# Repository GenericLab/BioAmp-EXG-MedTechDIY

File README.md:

Thanks a lot to the team at UpsideDown Labs!!!

## V1.0f - FeatherWing version, complete redesign for SMD 1206 parts

See more about the UM ESP-S3 board here: https://esp32s3.com/feathers3.html

## V1.0b - forked and ordered, in process of manufacturing

To be used in the future of our project week at HSLU: https://www.hackteria.org/wiki/Medizintechnik_DIY

Will be manufactured in GaudiLabs, still waiting for the parts... 0603 soooo small!!

Thanks a lot to the team at UpsideDown Labs!!!

# V1.0b - Original from Upside Down Labs

BioAmp EXG Pill is a small (2.54 X 1.00 cm) and elegant Analog Front End (AFE) board for BioPotential signal acquisition that you can use with any 5v Micro Controller Unit (MCU) with an ADC. It is capable of recording publication grade BioPotential signals like ECG, EMG, EOG, and EEG without the inclusion of any dedicated Hardware/Software filter, see [BioAmp EXG Pill v0.7 intro video](https://www.youtube.com/watch?v=-G3z9fvQnuw) for more info. The v1.0 of BioAmp EXG pill provides even more flexibilty with configuration option for Gain, BandPass, Filter, and Electrodes.

| Connection      |  Configuration |
| :-------------------------: | :-------------------------: |
|   | |

| Basic Arduino Circuit           |  Electromyography (EMG) |
| :-------------------------: | :-------------------------: |
|   | |

| Electrooculography (EOG) Horizontal           |  Electrooculography (EOG) Vertical |
| :-------------------------: | :-------------------------: |
|   | |

| Electrocardiography (ECG) Lead 1           |  Electroencephalography (EEG) |
| :-------------------------: | :-------------------------: |
|   | |

## Software
BioAmp EXG Pill works with any 5V microcontroller with an ADC like Arduino UNO/Nano or you can use dedicated 5v compatible ADC like ADS1115. To help with signal processing and cleaning you can use the included Arduino example sketches listed below.

| No. | Program| Description |
| ---- | ---- | ---- |
|1 | [FixedSampling](software/FixedSampling)| Sample from ADC at a fixed rate for easy processing of signal.|
|2 | [EMGFilter](software/EMGFilter)| A 74.5 - 149.5 Hz band pass filter sketch for clean Electromyography.|
|3 | [ECGFilter](software/ECGFilter)| A 0.5 - 44.5 Hz band-pass filter sketch for clean Electrocardiography.|
|4 | [EOGFilter](software/EOGFilter)| A 0.5 - 19.5 Hz band-pass filter sketch for clean Electrooculography.|
|5 | [EEGFilter](software/EEGFilter)| A 0.5 - 29.5 Hz band-pass filter sketch for clean Electroencephalography.|
|6 | [EMGEnvelop](software/EMGEnvelop)| EMG signal envelop detection for robotics and biomedical applications.|
|7 | [LEDBarGraph](software/LEDBarGraph)| LED bar graph showing EMG amplitude.|
|8 | [ServoControl](software/ServoControl)| Servo motor control with EMG.|
|9 | [HeartBeatDetection](software/HeartBeatDetection)| Standard deviation based heart beat detection algorithm.|
|10 | [EyeBlinkDetection](software/EyeBlinkDetection)|EOG based eye blink detection.|
|11 | [DrowsinessDetection](software/DrowsinessDetection)| Drowsiness detection using eye blink detection.|
|12 | [ClawController](software/ClawController)| Servo claw controller |
|13 | [EOGPhotoCaptureBLE](software/EOGPhotoCaptureBLE)| EOG based photo clicking machine using ESP32 BLE |

To-Do:

| No. | Program| Description |
| ---- | ---- | ---- |
|1 | HeartRate | Heart rate calculation with ECG.|
|2 | BrainWaves | Brain waves amplitude with FFT.|
|3 | EOGController | EOG based eye movement detection (left/right) to create a game controller.|

## Hardware

BioAmp EXG Pill has been created using KiCad and all the design files can be found under [hardware](hardware/) folder, including production [Gerber](hardware/gerbers) files. Images below shows a quick overview of the hardware design.

| PCB Front           |  PCB Back |
| :-------------------------: | :-------------------------: |
|   |  |

| Dimensions            |  Schematic  |
| :-------------------------: | :-------------------------: |
|   |  |

## License

| Licenses Facts              |  OSHWA Certification |
| :-------------------------: | :-------------------------: |
|   |  |

#### Hardware
CERN Open Hardware License Version 2 - Strongly Reciprocal ([CERN-OHL-S-2.0](https://spdx.org/licenses/CERN-OHL-S-2.0.html)).

#### Software
MIT open source [license](http://opensource.org/licenses/MIT).

#### Documentation:
<br />This work is licensed under a <a rel="license" href="http://creativecommons.org/licenses/by/4.0/">Creative Commons Attribution 4.0 International License</a>.

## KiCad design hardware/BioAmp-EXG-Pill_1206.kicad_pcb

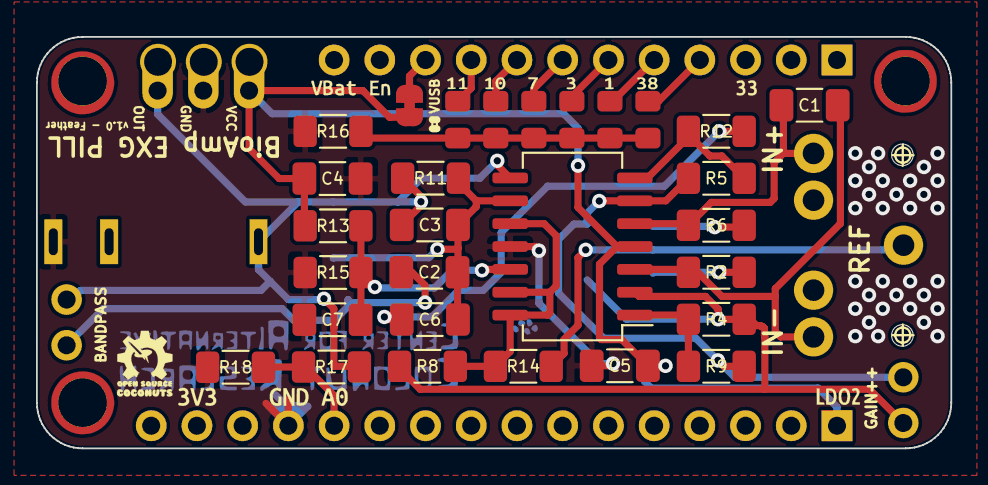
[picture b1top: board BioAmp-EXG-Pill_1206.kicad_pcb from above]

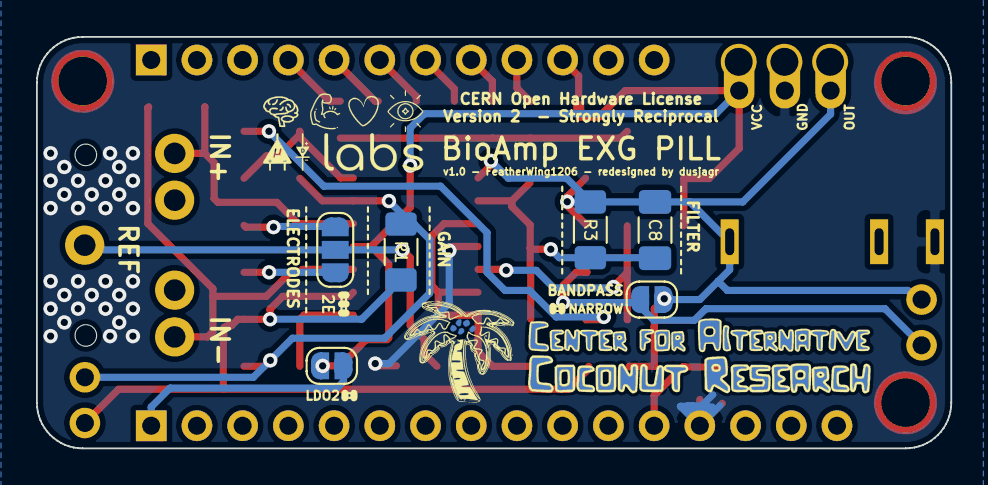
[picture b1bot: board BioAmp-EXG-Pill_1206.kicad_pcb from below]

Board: 2 copper layers, 50.8 x 22.9 mm, 47 parts (10 on the bottom side), 27 nets.

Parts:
BOARD1: FeaterWing Board; WeatherWing_empty
C1: 2.2nF; C_1206_dusjagr
C2, C3: 47nF; C_1206_dusjagr
C4: 100nF; C_1206_dusjagr
C5: 4.7uF; C_1206_dusjagr
C6: 47uF; C_1206_dusjagr
C7: 220nF; C_1206_dusjagr
C8: BPFC_C; C_1206_dusjagr
D1, D2, D3, D4, D5, D6: LED; LED_0805_2012Metric_Pad1.15x1.40mm_HandSolder
F1: feather long; PinHeader_1x16_FeatherLong
F2: feather short; PinHeader_1x12_FeatherShort
J1: BioAmp Output; BioAmp_PinHeader_1x03_P2.54mm_Vertical
J2: StressRelief Output; PinHeader_1x03_StressRelief
J3: AudioJack_Mono; PJ301M-12_dusjagr_3d
J4: AudioJack_TRS; AUDIO-Jack_3.5mm_5Pin
JP1: SolderJumper_3_Open; SolderJumper-3_P1.3mm_Open_RoundedPad1.0x1.5mm
JP2, JP6: SolderJumper_2_Open; SolderJumper-2_P1.3mm_Open_RoundedPad1.0x1.5mm
JP3, JP4: Jumper_NO_Small; PinHeader_1x02_P2.54mm_Vertical
JP5: SolderJumper_2_Bridged; SolderJumper-2_P1.3mm_Bridged
LOGO1: LOGO_UDLABS; LOGO-UpsideDownLabs-EXG
LOGO2: LOGO_Coconut; Coconut_logo
LOGO3: CoconutResearch; LOGO-CoconutText
R1: RG; R_1206_dusjagr
R2, R6, R11: 1M; R_1206_dusjagr
R3: BPFC_R; R_1206_dusjagr
R4, R9, R12, R17: 1K; R_1206_dusjagr
R5, R8, R13, R15: 10K; R_1206_dusjagr
R14: 1k; R_1206_dusjagr
R16: R; R_1206_dusjagr
R18: 2K2; R_1206_dusjagr
U1: TL074; SO-14_5.3x10.2mm_P1.27mm

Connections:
/A0: F1.12, R17.1, R18.1
/F1: D1.2, F2.4
/F2: D2.2, F2.5
/F3: D3.2, F2.6
/F4: D4.2, F2.7
/F5: D5.2, F2.8
/F6: D6.2, F2.9
/LDO2: F1.1, JP6.2
/VUSB: F2.10, JP5.2
DRL: J4.S, JP1.2, R14.1
GND: C4.1, C5.1, C7.2, F1.13, J1.2, J2.2, J3.S, R15.1, R16.1, R18.2, U1.11
IN+: C1.1, J4.T, R6.1, U1.5
IN-: C1.2, J4.R, R2.2, U1.3
unnamed: C2.1, JP2.1, JP3.1
unnamed: C6.2, R12.1
unnamed: C7.1, R13.1, R15.2, U1.12
unnamed: D1.1, D2.1, D3.1, D4.1, D5.1, D6.1, R16.2
unnamed: JP1.1, R2.1
unnamed: JP1.3, R6.2
unnamed: JP4.1, R1.2, R4.2, R8.1, U1.2
unnamed: JP4.2, R1.1, R5.2, R9.1, U1.6
unnamed: R4.1, R9.2, U1.1
OUT: C3.1, C8.1, J1.1, J2.1, J3.T, JP2.2, JP3.2, R3.1, R11.1, R17.2, U1.8
VCC: C4.2, C5.2, J1.3, J2.3, JP5.1, JP6.1, R13.2, U1.4
ampRef: R8.2, R14.2, U1.10, U1.13, U1.14
bpfIN: C2.2, C3.2, C6.1, C8.2, R3.2, R11.2, U1.9
inaOUT: R5.1, R12.2, U1.7

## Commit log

2022-09-15 redesigned PCB for manufacture MedTech style
2022-10-01 complete redesign for FeatherWint
2022-10-01 updating readme
2023-02-15 new bom and new ESP32 code
2023-09-14 new version for qtpy

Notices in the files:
README.md:
Open Source Licenses Facts  | Open Source Hardware Certification mark
